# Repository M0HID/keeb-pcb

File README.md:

# Keyboard - PCB

This is a keyboard PCB designed to accomodate cherry mx switches. It is a 65% layout (no function key row)
I created this keyboard as i didnt have any good reliable portable keyboard that was comfortable to type on, so by making this i hope to solve that.
I will create this PCB hopefully using hackclub onboard, and then assemble it myself

## Features
- Atmega 32U4 microcontroller
- USB-C!
- Rotary encoder (with switch!!)

## TODO
- Add RGB backlighting!!
- Oled screen (SSD1306 0.91")
- A case?

## Gallery

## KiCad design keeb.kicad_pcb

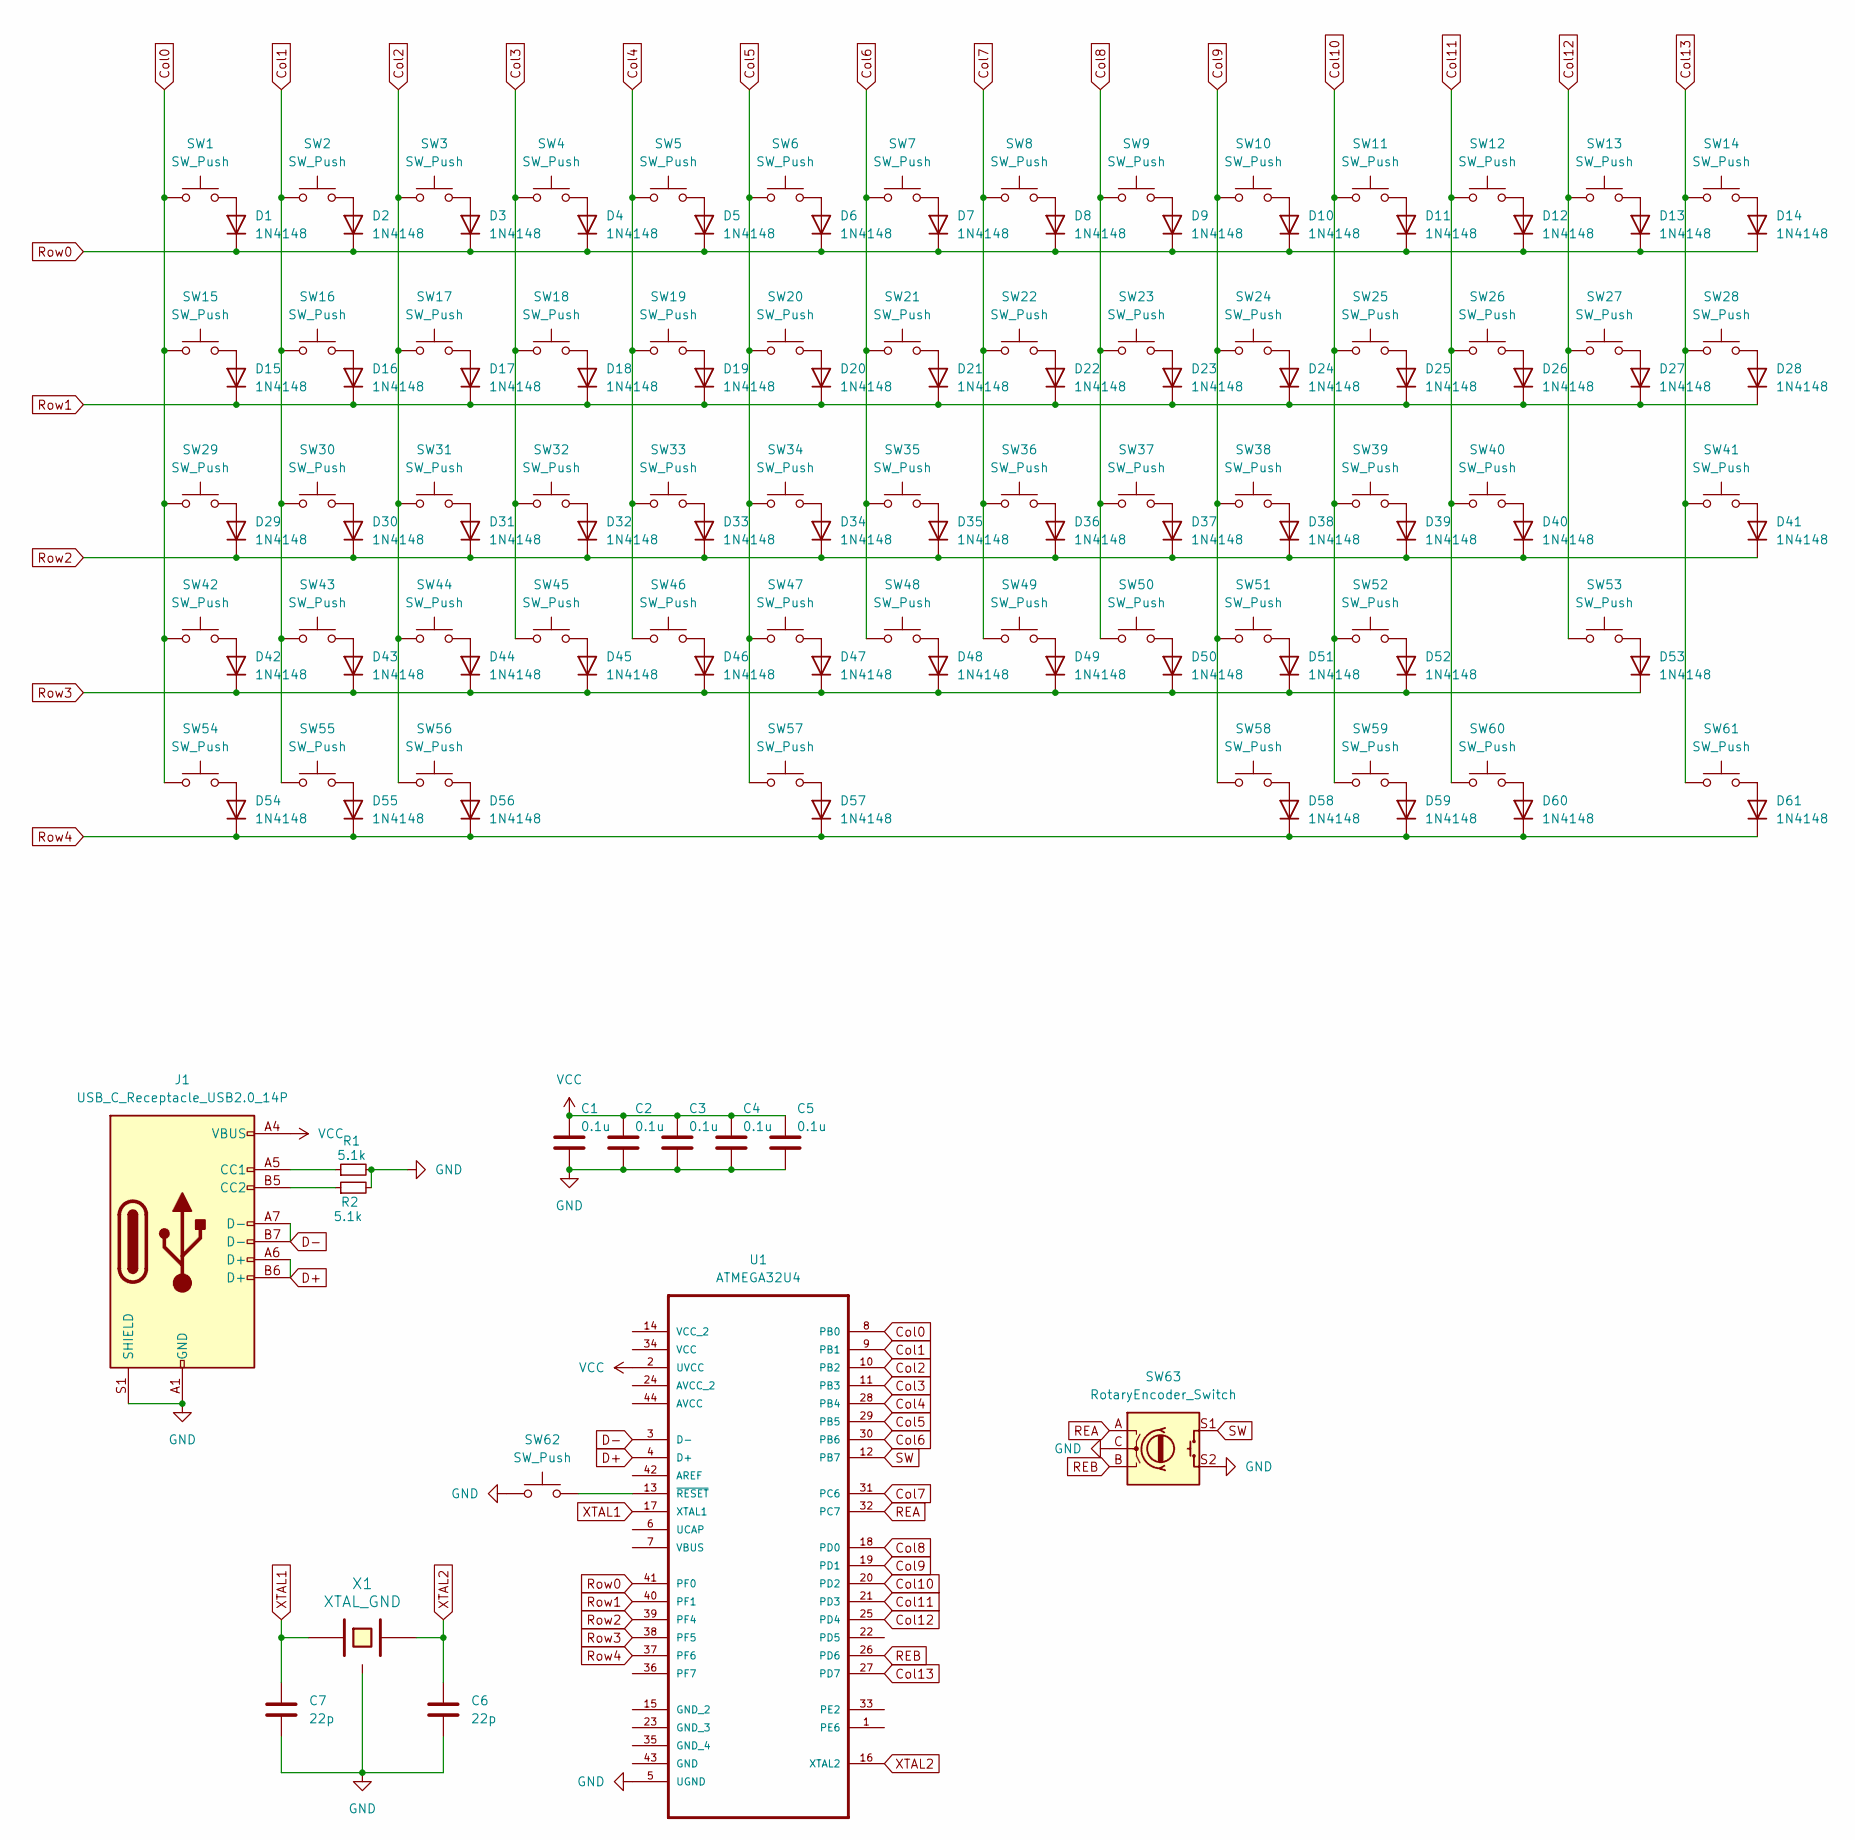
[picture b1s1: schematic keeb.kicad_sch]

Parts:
C1, C2, C3, C4, C5: 0.1u; C_0402_1005Metric_Pad0.74x0.62mm_HandSolder
C6, C7: 22p; C_0402_1005Metric_Pad0.74x0.62mm_HandSolder
D1, D2, D3, D4, D5, D6, D7, D8, D9, D10, D11, D12, D13, D14, D15, D16, D17, D18, D19, D20, D21, D22, D23, D24, D25, D26, D27, D28, D29, D30, D31, D32, D33, D34, D35, D36, D37, D38, D39, D40, D41, D42, D43, D44, D45, D46, D47, D48, D49, D50, D51, D52, D53, D54, D55, D56, D57, D58, D59, D60, D61: 1N4148; D_DO-35_SOD27_P7.62mm_Horizontal
J1: USB_C_Receptacle_USB2.0_14P; USB_C_Receptacle_GCT_USB4105-xx-A_16P_TopMnt_Horizontal
R1, R2: 5.1k; R_0402_1005Metric_Pad0.72x0.64mm_HandSolder
SW1, SW2, SW3, SW4, SW5, SW6, SW7, SW8, SW9, SW10, SW11, SW12, SW13, SW16, SW17, SW18, SW19, SW20, SW21, SW22, SW23, SW24, SW25, SW26, SW27, SW30, SW31, SW32, SW33, SW34, SW35, SW36, SW37, SW38, SW39, SW40, SW43, SW44, SW45, SW46, SW47, SW48, SW49, SW50, SW51, SW52: SW_Push; MX-Alps-Hybrid-1U
SW14: SW_Push; MX-Alps-Hybrid-2U
SW15, SW28: SW_Push; MX-Alps-Hybrid-1.5U
SW29: SW_Push; MX-Alps-Hybrid-1.75U
SW41, SW42: SW_Push; MX-Alps-Hybrid-2.25U
SW53: SW_Push; MX-Alps-Hybrid-2.75U
SW54, SW55, SW56, SW58, SW59, SW60, SW61: SW_Push; MX-Alps-Hybrid-1.25U
SW57: SW_Push; MX-Alps-Hybrid-6.25U
SW62: SW_Push; SW_SPST_TL3342
SW63: RotaryEncoder_Switch; RotaryEncoder_Alps_EC11E-Switch_Vertical_H20mm
U1: ATMEGA32U4; ATmega32U4
X1: XTAL_GND; XTAL_HC_49_TH

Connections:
Col0: SW1.1, SW15.1, SW29.1, SW42.1, SW54.1, U1.8 (PB0)
Col1: SW2.1, SW16.1, SW30.1, SW43.1, SW55.1, U1.9 (PB1)
Col2: SW3.1, SW17.1, SW31.1, SW44.1, SW56.1, U1.10 (PB2)
Col3: SW4.1, SW18.1, SW32.1, SW45.1, U1.11 (PB3)
Col4: SW5.1, SW19.1, SW33.1, SW46.1, U1.28 (PB4)
Col5: SW6.1, SW20.1, SW34.1, SW47.1, SW57.1, U1.29 (PB5)
Col6: SW7.1, SW21.1, SW35.1, SW48.1, U1.30 (PB6)
Col7: SW8.1, SW22.1, SW36.1, SW49.1, U1.31 (PC6)
Col8: SW9.1, SW23.1, SW37.1, SW50.1, U1.18 (PD0)
Col9: SW10.1, SW24.1, SW38.1, SW51.1, SW58.1, U1.19 (PD1)
Col10: SW11.1, SW25.1, SW39.1, SW52.1, SW59.1, U1.20 (PD2)
Col11: SW12.1, SW26.1, SW40.1, SW60.1, U1.21 (PD3)
Col12: SW13.1, SW27.1, SW53.1, U1.25 (PD4)
Col13: SW14.1, SW28.1, SW41.1, SW61.1, U1.27 (PD7)
D+: J1.A6 (D+), J1.B6 (D+), U1.4 (D+)
D-: J1.A7 (D-), J1.B7 (D-), U1.3 (D-)
GND: C1.2, C2.2, C3.2, C4.2, C5.2, C6.2, C7.2, J1.A1 (GND), J1.A12 (GND), J1.B1 (GND), J1.B12 (GND), J1.S1 (SHIELD), R1.2, R2.2, SW62.1, SW63.C, SW63.S2, U1.5 (UGND), X1.3
unnamed: D1.2 (A), SW1.2
unnamed: D2.2 (A), SW2.2
unnamed: D3.2 (A), SW3.2
unnamed: D4.2 (A), SW4.2
unnamed: D5.2 (A), SW5.2
unnamed: D6.2 (A), SW6.2
unnamed: D7.2 (A), SW7.2
unnamed: D8.2 (A), SW8.2
unnamed: D9.2 (A), SW9.2
unnamed: D10.2 (A), SW10.2
unnamed: D11.2 (A), SW11.2
unnamed: D12.2 (A), SW12.2
unnamed: D13.2 (A), SW13.2
unnamed: D14.2 (A), SW14.2
unnamed: D15.2 (A), SW15.2
unnamed: D16.2 (A), SW16.2
unnamed: D17.2 (A), SW17.2
unnamed: D18.2 (A), SW18.2
unnamed: D19.2 (A), SW19.2
unnamed: D20.2 (A), SW20.2
unnamed: D21.2 (A), SW21.2
unnamed: D22.2 (A), SW22.2
unnamed: D23.2 (A), SW23.2
unnamed: D24.2 (A), SW24.2
unnamed: D25.2 (A), SW25.2
unnamed: D26.2 (A), SW26.2
unnamed: D27.2 (A), SW27.2
unnamed: D28.2 (A), SW28.2
unnamed: D29.2 (A), SW29.2
unnamed: D30.2 (A), SW30.2
unnamed: D31.2 (A), SW31.2
unnamed: D32.2 (A), SW32.2
unnamed: D33.2 (A), SW33.2
unnamed: D34.2 (A), SW34.2
unnamed: D35.2 (A), SW35.2
unnamed: D36.2 (A), SW36.2
unnamed: D37.2 (A), SW37.2
unnamed: D38.2 (A), SW38.2
unnamed: D39.2 (A), SW39.2
unnamed: D40.2 (A), SW40.2
unnamed: D41.2 (A), SW41.2
unnamed: D42.2 (A), SW42.2
unnamed: D43.2 (A), SW43.2
unnamed: D44.2 (A), SW44.2
unnamed: D45.2 (A), SW45.2
unnamed: D46.2 (A), SW46.2
unnamed: D47.2 (A), SW47.2
unnamed: D48.2 (A), SW48.2
unnamed: D49.2 (A), SW49.2
unnamed: D50.2 (A), SW50.2
unnamed: D51.2 (A), SW51.2
unnamed: D52.2 (A), SW52.2
unnamed: D53.2 (A), SW53.2
unnamed: D54.2 (A), SW54.2
unnamed: D55.2 (A), SW55.2
unnamed: D56.2 (A), SW56.2
unnamed: D57.2 (A), SW57.2
unnamed: D58.2 (A), SW58.2
unnamed: D59.2 (A), SW59.2
unnamed: D60.2 (A), SW60.2
unnamed: D61.2 (A), SW61.2
unnamed: J1.A5 (CC1), R1.1
unnamed: J1.B5 (CC2), R2.1
unnamed: SW62.2, U1.13 (~RESET)
REA: SW63.A, U1.32 (PC7)
REB: SW63.B, U1.26 (PD6)
Row0: D1.1 (K), D2.1 (K), D3.1 (K), D4.1 (K), D5.1 (K), D6.1 (K), D7.1 (K), D8.1 (K), D9.1 (K), D10.1 (K), D11.1 (K), D12.1 (K), D13.1 (K), D14.1 (K), U1.41 (PF0)
Row1: D15.1 (K), D16.1 (K), D17.1 (K), D18.1 (K), D19.1 (K), D20.1 (K), D21.1 (K), D22.1 (K), D23.1 (K), D24.1 (K), D25.1 (K), D26.1 (K), D27.1 (K), D28.1 (K), U1.40 (PF1)
Row2: D29.1 (K), D30.1 (K), D31.1 (K), D32.1 (K), D33.1 (K), D34.1 (K), D35.1 (K), D36.1 (K), D37.1 (K), D38.1 (K), D39.1 (K), D40.1 (K), D41.1 (K), U1.39 (PF4)
Row3: D42.1 (K), D43.1 (K), D44.1 (K), D45.1 (K), D46.1 (K), D47.1 (K), D48.1 (K), D49.1 (K), D50.1 (K), D51.1 (K), D52.1 (K), D53.1 (K), U1.38 (PF5)
Row4: D54.1 (K), D55.1 (K), D56.1 (K), D57.1 (K), D58.1 (K), D59.1 (K), D60.1 (K), D61.1 (K), U1.37 (PF6)
SW: SW63.S1, U1.12 (PB7)
VCC: C1.1, C2.1, C3.1, C4.1, C5.1, J1.A4 (VBUS), J1.A9 (VBUS), J1.B4 (VBUS), J1.B9 (VBUS), U1.2 (UVCC)
XTAL1: C7.1, U1.17 (XTAL1), X1.1
XTAL2: C6.1, U1.16 (XTAL2), X1.2

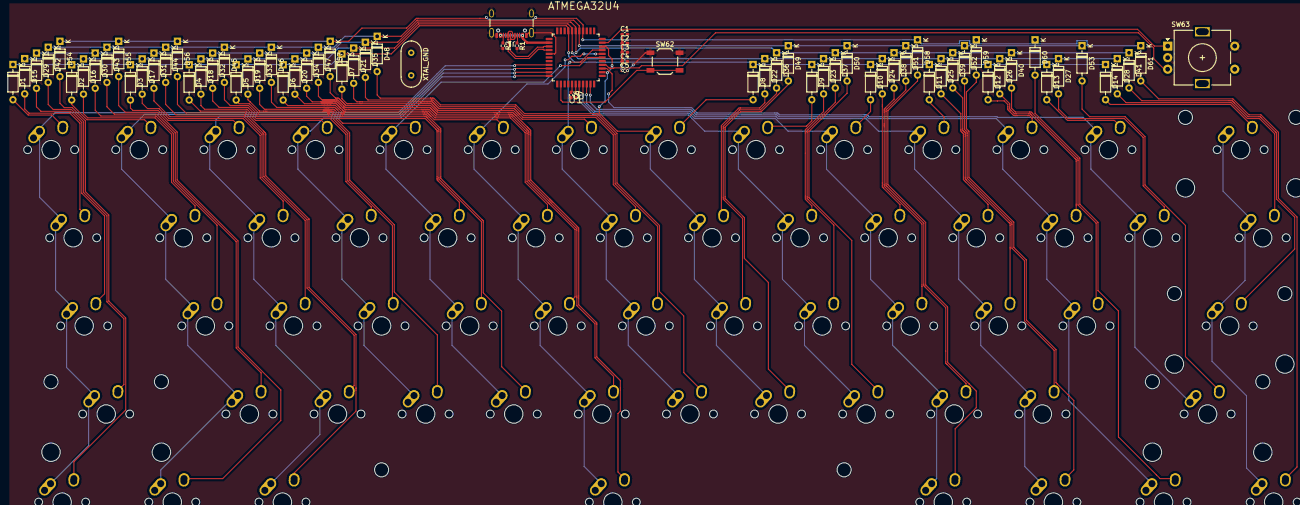
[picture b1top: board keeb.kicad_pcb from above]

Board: 2 copper layers, 136 parts (0 on the bottom side), 92 nets.

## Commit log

2025-02-01 add files
